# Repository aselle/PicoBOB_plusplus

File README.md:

# PicoBOB++ for GRBLHAL and one day LinuxCNC

*This repo is for experimentation. If you want easy nice experience stick with the PicoBOB for now at (https://github.com/Expatria-Technologies/PicoBOB)*

PicoBOB++ is currently an experimental design which is based on Experia's PicoBOB. The primary goals are

The design here is located in PicoBOB_plus_plus and is in KiCad

* Allow using LinuxCNC as well as GrblHal with ideally no rewiring
  * Pins are reassigned to allow SPI to enable LinuxCNC
  * Connects to Raspberry PI via header.
* Use KiCad because I don't have Altium and know hot o use KiCad

Notes

* Unlike PicoBOB RevB, I have gone back to using a Pi Pico devboard. I do not solder with the castellations but use a header placement approach. This simplifies board assembly by hand, and it allows more flexibility to revise while I'm playing with the hardware.
* Uses bigger SMD (0805) and some TH parts currently just because of what I had laying around.
* This is not supported in anyway.
* If you want to have an easy time buy an Experia, see below.

Software

* GrblHal modifications needed for this pinout are in https://github.com/aselle/grblhal-RP2040/tree/picobob_plusplus

Photos

# PicoBOB for GRBLHAL

Expatria Technologies PicoBOB GRBLHAL module

Currently available in our online store:

https://expatria.myshopify.com/products/picobob

Please consider buying a board to support our open-source designs. 

The PicoBOB allows you to use the high performance GRBLHAL motion control system with a traditional Mach3/LinuxCNC parallel-port breakout board.  It is intended to be simple and low cost.  It uses a Raspberry Pi RP2040 MCU and the widely available 5 axis Mach3 breakout board.  The PicoBOB can be easily sourced from JLCPCB.  The complete BOM and fabrications files are in the CAM_OUTPUTS folder for upload.  The design is free to use by all parties, including commercial parties, under the CERN-OHL-S V2 license.  It is our hope that the community finds the design useful and that it may be carried forward to help advance the PrintNC and broader CNC hobby community.

The PicoBOB closely tracks the features of the Mach3 BOB:

1) Up to 5 axes of step/direction control.
3) 10A Spindle relay control.
4) 0-10V analog spindle speed control.
5) 5 general purpose inputs
6) One general purpose output.

The default GRBLHAL builds for the PicoBOB include the following features that are implemented in the RP2040 port of GRBLHAL:

1) Backlash Compensation.
2) Stress-free Autosquaring for the ganged axis
3) Ganged axis offsets to correct for offset homing switches
4) Step rates tested up to 180 KHz on 5 simultaneous axes.

In addition, the board has a USB micro connector for the 5V that is required for the BOB.  There is also a push button to reset the Pi Pico without disconnecting power.

Gerber output files are in the CAM_OUTPUTS folder, along with BOM and Pick and Place files to facilitate easy ordering from JLCPCB.  Now available as a chip-down design in revision B1.  Older A1 revision for Pi Pico module is still hosted in case you want to do the final soldering by hand.  The two designs are functionally identical.

## PicoBOB Overview

Usage notes:

Communication with GRBLHAL on the PicoBOB is accomplished via the USBC connection on the PicoBOB (not connected in above images).  A short USB cable is used to provide the required 5V for the BOB.  In addition, the BOB requires an external 12-24V supply.

The Mach3 BOB shares the B axis direction signal with a spindle relay enable signal - only one can be used at a time.  Also on the PicoBOB, the stepper enable signal is modified in the GRBLHAL default map file so that it is used as the coolant output signal.  All of this is configurable by re-building the GRBLHAL firwmare.

Above shows the PicoBOB A1 with a Pi Pico installed and connected to the Mach3/LinuxCNC parallel BOB.

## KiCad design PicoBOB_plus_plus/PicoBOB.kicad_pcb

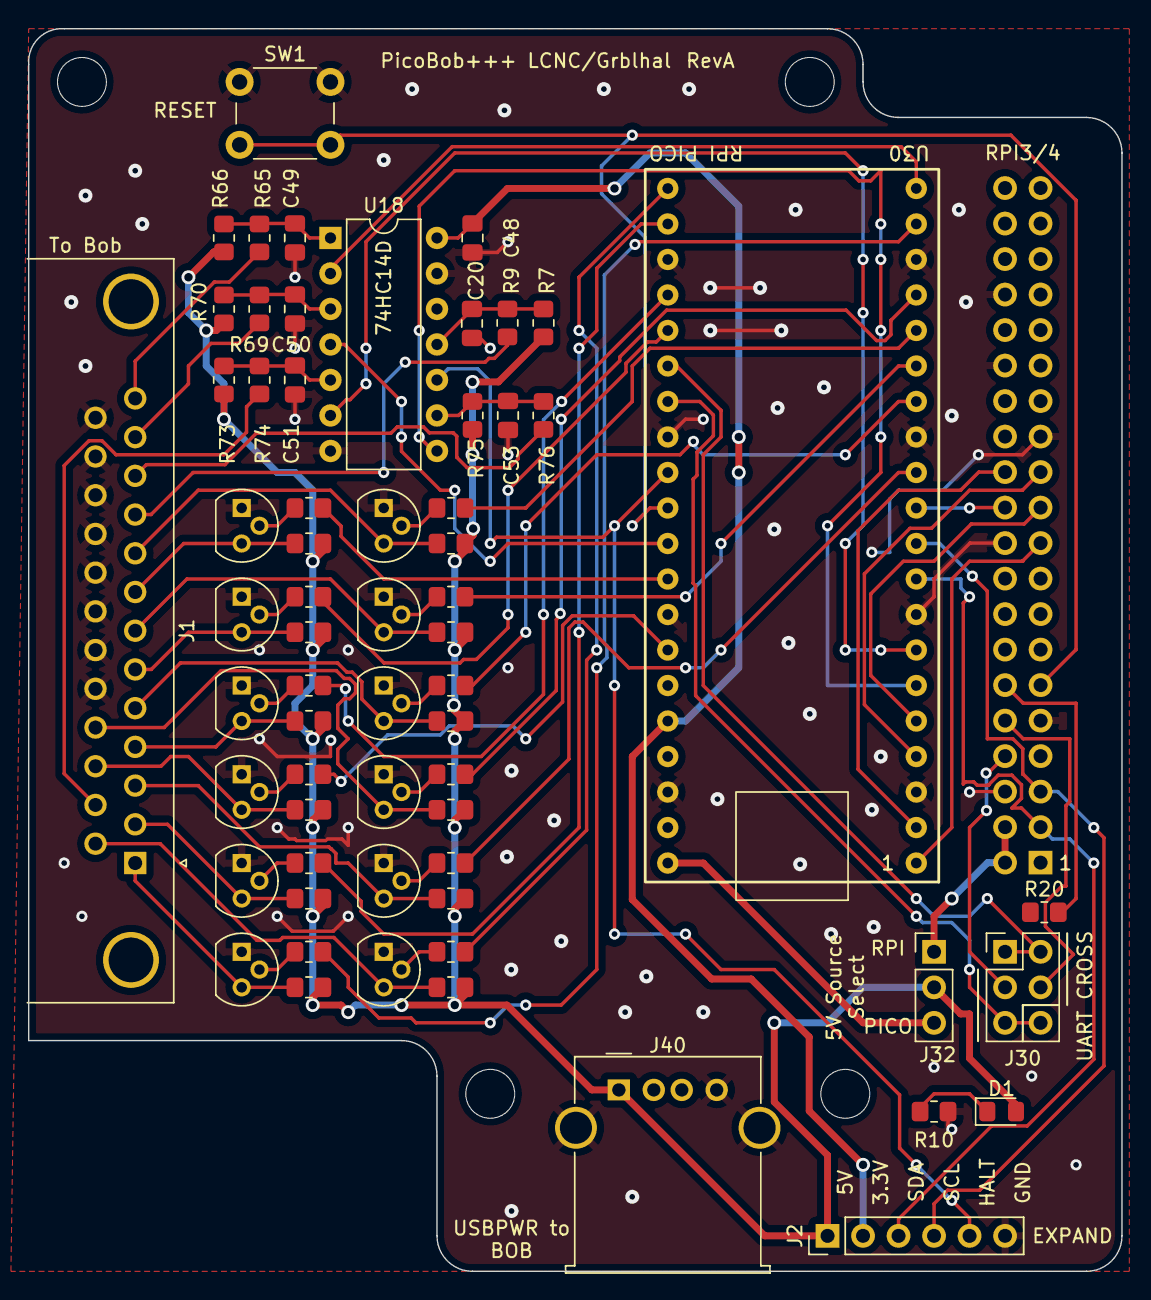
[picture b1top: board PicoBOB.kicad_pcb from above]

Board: 2 copper layers, 78.2 x 88.9 mm, 64 parts (1 on the bottom side), 70 nets.

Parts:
C20, C49, C50, C51, C53: 10nF; C_0805_2012Metric_Pad1.18x1.45mm_HandSolder
C48: 1.0uF; C_0805_2012Metric_Pad1.18x1.45mm_HandSolder
D1: LED; LED_0805_2012Metric_Pad1.15x1.40mm_HandSolder
J1: D-DMR025PF-D002; DSUB-25_Female_Horizontal_P2.77x2.84mm_EdgePinOffset4.94mm_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
J2: Conn_01x06_Male; PinHeader_1x06_P2.54mm_Vertical
J30: Conn_02x03_Odd_Even; PinHeader_2x03_P2.54mm_Vertical
J31: Raspberry_Pi_2_3; RaspberryPi
J32: Conn_01x03_Male; PinHeader_1x03_P2.54mm_Vertical
J40: USB_A; USB_A_Molex_67643_Horizontal
Q_Ad_13: 2n3904; TO-92
Q_As_13: 2n3904; TO-92
Q_Bd_13: 2n3904; TO-92
Q_Bs_13: 2n3904; TO-92
Q_EN_13: 2n3904; TO-92
Q_PWM_13: 2n3904; TO-92
Q_Xd_13: 2n3904; TO-92
Q_Xs_13: 2n3904; TO-92
Q_Yd_13: 2n3904; TO-92
Q_Ys_13: 2n3904; TO-92
Q_Zd_13: 2n3904; TO-92
Q_Zs_13: 2n3904; TO-92
R7, R65, R69, R73, R75: 100KΩ ±1%; R_0805_2012Metric_Pad1.20x1.40mm_HandSolder
R9, R66, R70, R74, R76: 510Ω ±1%; R_0805_2012Metric_Pad1.20x1.40mm_HandSolder
R10: 5.1KΩ ±1%; R_0805_2012Metric_Pad1.20x1.40mm_HandSolder
R20: 0; R_0805_2012Metric_Pad1.20x1.40mm_HandSolder
R_Ad_56: 510Ω ±1%; R_0805_2012Metric_Pad1.20x1.40mm_HandSolder
R_Ad_83: 2.2kΩ ±1%; R_0805_2012Metric_Pad1.20x1.40mm_HandSolder
R_As_56: 510Ω ±1%; R_0805_2012Metric_Pad1.20x1.40mm_HandSolder
R_As_83: 2.2kΩ ±1%; R_0805_2012Metric_Pad1.20x1.40mm_HandSolder
R_Bd_56: 510Ω ±1%; R_0805_2012Metric_Pad1.20x1.40mm_HandSolder
R_Bd_83: 2.2kΩ ±1%; R_0805_2012Metric_Pad1.20x1.40mm_HandSolder
R_Bs_56: 510Ω ±1%; R_0805_2012Metric_Pad1.20x1.40mm_HandSolder
R_Bs_83: 2.2kΩ ±1%; R_0805_2012Metric_Pad1.20x1.40mm_HandSolder
R_EN_56: 510Ω ±1%; R_0805_2012Metric_Pad1.20x1.40mm_HandSolder
R_EN_83: 2.2kΩ ±1%; R_0805_2012Metric_Pad1.20x1.40mm_HandSolder
R_PWM_56: 510Ω ±1%; R_0805_2012Metric_Pad1.20x1.40mm_HandSolder
R_PWM_83: 2.2kΩ ±1%; R_0805_2012Metric_Pad1.20x1.40mm_HandSolder
R_Xd_56: 510Ω ±1%; R_0805_2012Metric_Pad1.20x1.40mm_HandSolder
R_Xd_83: 2.2kΩ ±1%; R_0805_2012Metric_Pad1.20x1.40mm_HandSolder
R_Xs_56: 510Ω ±1%; R_0805_2012Metric_Pad1.20x1.40mm_HandSolder
R_Xs_83: 2.2kΩ ±1%; R_0805_2012Metric_Pad1.20x1.40mm_HandSolder
R_Yd_56: 510Ω ±1%; R_0805_2012Metric_Pad1.20x1.40mm_HandSolder
R_Yd_83: 2.2kΩ ±1%; R_0805_2012Metric_Pad1.20x1.40mm_HandSolder
R_Ys_56: 510Ω ±1%; R_0805_2012Metric_Pad1.20x1.40mm_HandSolder
R_Ys_83: 2.2kΩ ±1%; R_0805_2012Metric_Pad1.20x1.40mm_HandSolder
R_Zd_56: 510Ω ±1%; R_0805_2012Metric_Pad1.20x1.40mm_HandSolder
R_Zd_83: 2.2kΩ ±1%; R_0805_2012Metric_Pad1.20x1.40mm_HandSolder
R_Zs_56: 510Ω ±1%; R_0805_2012Metric_Pad1.20x1.40mm_HandSolder
R_Zs_83: 2.2kΩ ±1%; R_0805_2012Metric_Pad1.20x1.40mm_HandSolder
SW1: SKRTLAE010; SW_PUSH_6mm
U18: 74HC14D; DIP-14_W7.62mm
U30: PICO; RPI_PICO

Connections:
+3.3V: C48.1, J2.2, U18.14 (VCC), U30.36 (3v3(out))
+5V: D1.2 (A), J2.1, J32.2, J40.1 (VBUS), R7.2, R65.2, R69.2, R73.2, R75.2, R_Ad_56.2, R_As_56.2, R_Bd_56.2, R_Bs_56.2, R_EN_56.2, R_PWM_56.2, R_Xd_56.2, R_Xs_56.2, R_Yd_56.2, R_Ys_56.2, R_Zd_56.2, R_Zs_56.2
/DIR_A: R_Ad_83.1, U30.16 (GP12)
/DIR_A_5V: J1.9, Q_Ad_13.3 (C), R_Ad_56.1
/DIR_B: R_Bd_83.1, U30.17 (GP13)
/DIR_B_5V: J1.17, Q_Bd_13.3 (C), R_Bd_56.1
/DIR_X: R_Xd_83.1, U30.12 (GP9)
/DIR_X_5V: J1.3, Q_Xd_13.3 (C), R_Xd_56.1
/DIR_Y: R_Yd_83.1, U30.14 (GP10)
/DIR_Y_5V: J1.5, Q_Yd_13.3 (C), R_Yd_56.1
/DIR_Z: R_Zd_83.1, U30.15 (GP11)
/DIR_Z_5V: J1.7, Q_Zd_13.3 (C), R_Zd_56.1
/HALT: J2.5, U18.10 (Y), U30.29 (GP22)
/HALT_5V: J1.10, R9.1
/PICO_5V: J32.3, U30.40 (VBUS)
/PICO_RUN: J31.11 (GPIO17), SW1.2, U30.30 (RUN)
/PROBE: U18.8 (Y), U30.6 (GP4)
/PROBE_5V: J1.11, R76.1
/PRU_RESET: J31.22 (GPIO25), U30.11 (GP8)
/RPI_5V: J31.2 (5V), J31.4 (5V), J32.1
/RXD_INT: J30.5, J30.6, U30.27 (GP21)
/RXD_PI: J30.4, J31.10 (GPIO15/RXD)
/SCL: J2.4, J31.5 (SCL/GPIO3), U30.10 (GP7)
/SDA: J2.3, J31.3 (SDA/GPIO2), U30.9 (GP6)
/SPINDLE_PWM: R_PWM_83.1, U30.19 (GP14)
/SPINDLE_PWM_5V: J1.1, Q_PWM_13.3 (C), R_PWM_56.1
/SPI_CLK: J31.23 (SCLK0/GPIO11), U30.4 (GP2)
/SPI_CS_JOG_SW: J31.24 (~CE0/GPIO8), U30.2 (GP1)
/SPI_MISO: J31.21 (MISO0/GPIO9), U30.5 (GP3)
/SPI_MOSI: J31.19 (MOSI0/GPIO10), U30.1 (GP0)
/STEP_A: R_As_83.1, U30.32 (GP27_A1)
/STEP_A_5V: J1.8, Q_As_13.3 (C), R_As_56.1
/STEP_B: R_Bs_83.1, U30.34 (GP28_A2)
/STEP_B_5V: J1.16, Q_Bs_13.3 (C), R_Bs_56.1
/STEP_X: R_Xs_83.1, U30.22 (GP17)
/STEP_X_5V: J1.2, Q_Xs_13.3 (C), R_Xs_56.1
/STEP_Y: R_Ys_83.1, U30.24 (GP18)
/STEP_Y_5V: J1.4, Q_Ys_13.3 (C), R_Ys_56.1
/STEP_Z: R_Zs_83.1, U30.25 (GP19)
/STEP_Z_5V: J1.6, Q_Zs_13.3 (C), R_Zs_56.1
/STP_EN_XYZAB: R_EN_83.1, U30.21 (GP16)
/STP_EN_XYZAB_5V: J1.14, Q_EN_13.3 (C), R_EN_56.1
/TXD_INT: J30.1, J30.2, U30.26 (GP20)
/TXD_PI: J30.3, J31.8 (GPIO14/TXD)
/X_LIM: U18.4 (Y), U30.31 (GP26_A0)
/X_LIM_5V: J1.12, R70.1
/Y_LIM: U18.2 (Y), U30.20 (GP15)
/Y_LIM_5V: J1.13, R66.1
/Z_LIM: U18.6 (Y), U30.7 (GP5)
/Z_LIM_5V: J1.15, R74.1
GND: C20.1, C48.2, C49.1, C50.1, C51.1, C53.1, J1.18, J1.19, J1.20, J1.21, J1.22, J1.23, J1.24, J1.25, J2.6, J31.6 (GND), J31.9 (GND), J31.14 (GND), J31.20 (GND), J31.25 (GND), J31.30 (GND), J31.34 (GND), J31.39 (GND), J40.4 (GND), J40.5 (Shield), Q_Ad_13.1 (E), Q_As_13.1 (E), Q_Bd_13.1 (E), Q_Bs_13.1 (E), Q_EN_13.1 (E), Q_PWM_13.1 (E), Q_Xd_13.1 (E), Q_Xs_13.1 (E), Q_Yd_13.1 (E), Q_Ys_13.1 (E), Q_Zd_13.1 (E), Q_Zs_13.1 (E), R10.2, SW1.1, U18.7 (GND), U18.13 (A), U30.3 (GND_1), U30.8 (GND_2), U30.13 (GND_3), U30.18 (GND_4), U30.23 (GND_5), U30.28 (GND_6), U30.33 (GND_7), U30.38 (GND_8)
unnamed: C20.2, R7.1, R9.2, U18.11 (A)
unnamed: C49.2, R65.1, R66.2, U18.1 (A)
unnamed: C50.2, R69.1, R70.2, U18.3 (A)
unnamed: C51.2, R73.1, R74.2, U18.5 (A)
unnamed: C53.2, R75.1, R76.2, U18.9 (A)
unnamed: D1.1 (K), R10.1
unnamed: J31.12 (GPIO18/PWM0), R20.2
unnamed: Q_Ad_13.2 (B), R_Ad_83.2
unnamed: Q_As_13.2 (B), R_As_83.2
unnamed: Q_Bd_13.2 (B), R_Bd_83.2
unnamed: Q_Bs_13.2 (B), R_Bs_83.2
unnamed: Q_EN_13.2 (B), R_EN_83.2
unnamed: Q_PWM_13.2 (B), R_PWM_83.2
unnamed: Q_Xd_13.2 (B), R_Xd_83.2
unnamed: Q_Xs_13.2 (B), R_Xs_83.2
unnamed: Q_Yd_13.2 (B), R_Yd_83.2
unnamed: Q_Ys_13.2 (B), R_Ys_83.2
unnamed: Q_Zd_13.2 (B), R_Zd_83.2
unnamed: Q_Zs_13.2 (B), R_Zs_83.2

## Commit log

2022-10-30 PicoBOB++ Experimental Board using Kicad Based on PicoBOB
    * Make kicad board
    * Remap pins to allow SPI
    * Relayout with larger smd parts
    * Add expansion i2c header
    * Add Header for Mounting Pico board
    * Add Header for Mounting RPI 3b or 4
2022-10-30 Edit Readme and add images
    * Add another note to the README about not using inline rp2040
    and instead go to using RPI Pico
    * Add imagery
